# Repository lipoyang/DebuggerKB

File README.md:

DebuggerKB
=========

## 概要
IDEでのデバッグ関連のショートカットキーを並べた専用キーボードです。

* 有線接続(USB HID)と無線接続(BLE HID)の両方に対応。
* LiPoバッテリー(400mAh)と充電回路を内蔵。
* キーマップは最大8レイヤーまで登録でき、切替キーでレイヤーを切り替え可能。
* キーマップはUSB接続時にWebアプリから設定可能。<br>(PC版の Chrome や Edge など Web Serial API に対応したブラウザが必要)
* Nordic nRF52840 搭載。 (Seeed Studio XIAO nRF52840)
* Arduinoベースの独自ファームウェア。 (QMKではありません。)

## キーマップの設定
[Webアプリ](app/DebuggerKB_Config/)から、各レイヤーの名称、LED表示色、キーマップを設定できます。

キーボードをUSB接続すると、HIDと仮想COMポートの複合デバイスになるので、Webアプリから仮想COMポートを選択して接続します。

## デフォルトのキーマップ
初期状態では4つのレイヤーが登録されています。

| キー | 機能名 (例) |Visual Studio | Eclipse | Android Studio | MPLAB X |
| ---- | ---- | ---- | ---- | ---- |---- |
|     | Debug        | F5            | F11      | Shift+F9  | 割当なし |
|       | Run          | Ctrl+F5       | Ctrl+F11 | Shift+F10 | 割当なし |
|  | Continue     | F5            | F8       | F9        | F5      |
|     | Pause        | Ctrl+Alt+Pause| 割当なし  | 割当なし  | Ctrl+Alt+8 |
|      | Stop         | Shift+F5      | Ctrl+F2  | Ctrl+F2   | Shift+F5 |
|  | Step Over    | F10           | F6       | F8        | F8      |
|    | Step Into    | F11           | F5       | F7        | F7      |
|   | Steo Out     | Shift+F11     | F7       | Shift+F8  | Ctrl+F7 |
|     | Run To Cursol| Ctrl+F10      | Ctrl+R   | Alt+F9    | F4      |
|   | Restart      | Ctrl+Shift+F5 | 割当なし  | 割当なし  | 割当なし |

※ 機能名はIDEによって異同があります。詳しくは[こちら](FunctionName.xlsx)。  
※ Pauseキー = Breakキー 

 と  を同時に押しながらUSBケーブルを接続するとキーマップがデフォルト設定に初期化されます。

## キースイッチとキーキャップについて
* キースイッチは Cherry MX スイッチ互換の Keilh BOX スイッチを使用しました。
* デバッガの操作という用途を考慮し、軸種はクリック感のある茶軸を選びました。
* [Kailh Switch Socket](https://shop.yushakobo.jp/products/a01ps) を使用しており、キースイッチの着脱が可能です。
* パターン設計の都合で、キースイッチの向きは North Facing (LED穴が上側) にしました。
* キーキャップは、DSAプロファイルのものを使用しました。
* キーキャップの印字は、[遊舎工房](https://yushakobo.jp/)さんのキーキャップUVプリントサービスを利用しました。
* キーキャップの印字データは、白キーキャップを前提として作成しました。(下地の白インクのデータ無し)

## 筐体について
* ボトムプレートとトッププレートは厚さ2mmのアクリル板(キャスト材)を使用しました。
* アクリル板の加工は、[工房Emerge+](https://www.emergeplus.jp/)さんのレーザー加工サービスを利用しました。
* 四隅の穴はM2ネジ用です。

## プリント基板について
* 基板製造は[PCBGOGO](https://www.pcbgogo.jp/)さんのサービスを利用しました。
* 厚さ1.6mmの両面基板で製造しました。
* 実装は手ハンダです。Seeed XIAO nRF52840 の裏面パッドはスルーホールからハンダ付けしました。

## ファームウェアについて

* ファームウェアは Arduinoベースで作成しました。
* Arduino IDEの「ファイル」＞「環境設定」＞「追加のボードマネージャのURL」に下記URLを追加します。
```
https://files.seeedstudio.com/arduino/package_seeeduino_boards_index.json
```
* 「ツール」＞「ボード」＞「ボードマネージャ」で「Seeed nRF52 Boards」をインストールします。
* 「ツール」＞「ボード」で Seeed nRF52 Boards > Seeed XIAO nRF52840 を選択します。
* Seeed nRF52 mbed-enabled Boards ではないことに注意してください。
* シリアルポートが認識しないときは、USBコネクタの横の小さなリセットボタン(RSTのシルクあり)をダブルクリックしてください。

## 依存ライブラリ
<table>
<tr><td>Adafruit NeoPixel </td><td>要インストール</td></tr>
<tr><td>Adafruit TinyUSB  </td><td>Seeed nRF52 Boards に付属</td></tr>
<tr><td>Adafruit_LittleFS </td><td>Seeed nRF52 Boards に付属</td></tr>
<tr><td>InternalFileSystem</td><td>Seeed nRF52 Boards に付属</td></tr>
<tr><td>Bluefruit         </td><td>Seeed nRF52 Boards に付属</td></tr>
</table>

## ファイル一覧

* hard/
    * DebuggerKB.sch/brd : 回路/基板設計データ(Eagle形式)
    * DebuggerKB.pdf : 回路図(PDF)
    * DebuggerKB.zip : ガーバーデータの圧縮ファイル
    * DebuggerKB_BOM.xlsx : BOMリスト(Excel形式)
* mecha/
    * A5_DebuggerKB.svg : プレート(アクリル板)の加工データ
    * DSA_1u_4x4_DebuggerKB.svg : キーキャップのUV印刷データ
* firm/DebuggerKB/
    * DebuggerKB.ino : キーボードのファームウェア (Arduinoスケッチ)
    * \*.h, \*.cpp: ファームウェアで使用する各種クラス宣言と実装
* app/DebuggerKB_Config/ 
    * index.html : キーマップ設定アプリ (webアプリ)
    * \*.js, \*.png, css/\*, lib/\* : キーマップ設定アプリで使用する各種ファイル

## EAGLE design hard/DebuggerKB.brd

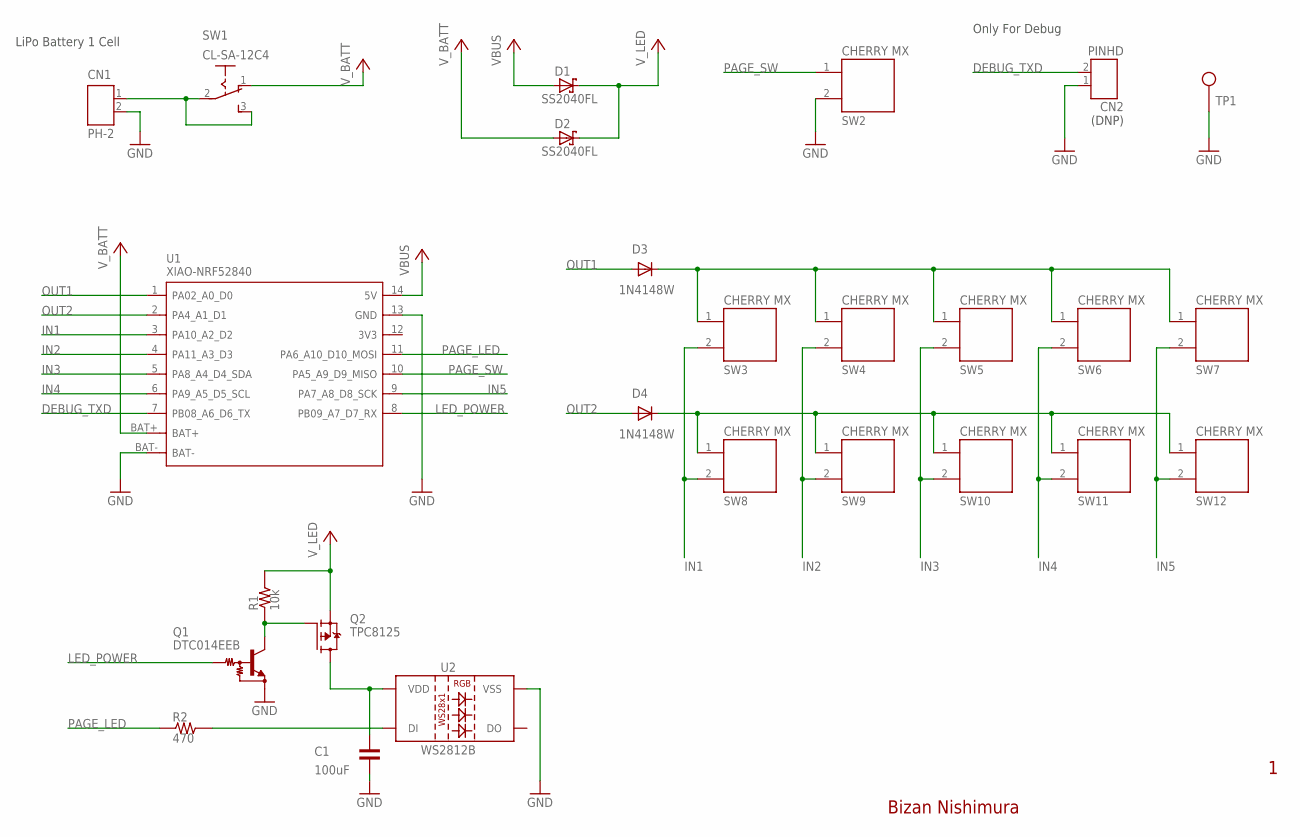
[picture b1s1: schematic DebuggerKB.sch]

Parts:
C1: 100uF; CP3216
CN1: PH-2
CN2: PINHD; 1X02
D1, D2: SS2040FL; SOD123
D3, D4: 1N4148W; SOD123
Q1: DTC014EEB; SOT490
Q2: TPC8125; SO-8
R1: 10k; CP1608
R2: 470; CP1608
SW1: CL-SA-12C4
SW2, SW3, SW4, SW5, SW6, SW7, SW8, SW9, SW10, SW11, SW12: KAILH_SWITCH_SOCKET; SWITCH_SOCKET
TP1: TEST_PIN
U1: XIAO-NRF52840; XIAO-NRF52840-BAT
U2: WS2812B

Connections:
DEBUG_TXD: CN2.2, U1.7 (PB08_A6_D6_TX)
GND: C1.SMD2 (PIN2), CN1.2, CN2.1, Q1.2 (E), SW2.2 (PIN-2), TP1.1, U1.13 (GND), U1.BAT-, U2.3 (VSS)
IN1: SW3.2 (PIN-2), SW8.2 (PIN-2), U1.3 (PA10_A2_D2)
IN2: SW4.2 (PIN-2), SW9.2 (PIN-2), U1.4 (PA11_A3_D3)
IN3: SW5.2 (PIN-2), SW10.2 (PIN-2), U1.5 (PA8_A4_D4_SDA)
IN4: SW6.2 (PIN-2), SW11.2 (PIN-2), U1.6 (PA9_A5_D5_SCL)
IN5: SW7.2 (PIN-2), SW12.2 (PIN-2), U1.9 (PA7_A8_D8_SCK)
LED_POWER: Q1.1 (B), U1.8 (PB09_A7_D7_RX)
unnamed: C1.SMD1 (PIN1), Q2.5 (D), Q2.6 (D), Q2.7 (D), Q2.8 (D), U2.1 (VDD)
unnamed: CN1.1, SW1.2, SW1.3 (S)
unnamed: Q1.3 (C), Q2.4 (G), R1.SMD1 (PIN1)
unnamed: R2.SMD2 (PIN2), U2.4 (DI)
unnamed: D3.C, SW3.1 (PIN-1), SW4.1 (PIN-1), SW5.1 (PIN-1), SW6.1 (PIN-1), SW7.1 (PIN-1)
unnamed: D4.C, SW8.1 (PIN-1), SW9.1 (PIN-1), SW10.1 (PIN-1), SW11.1 (PIN-1), SW12.1 (PIN-1)
OUT1: D3.A, U1.1 (PA02_A0_D0)
OUT2: D4.A, U1.2 (PA4_A1_D1)
PAGE_LED: R2.SMD1 (PIN1), U1.11 (PA6_A10_D10_MOSI)
PAGE_SW: SW2.1 (PIN-1), U1.10 (PA5_A9_D9_MISO)
VBUS: D1.A, U1.14 (5V)
V_BATT: D2.A, SW1.1 (O), U1.BAT+
V_LED: D1.C, D2.C, Q2.1 (S), Q2.2 (S), Q2.3 (S), R1.SMD2 (PIN2)

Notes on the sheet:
Bizan Nishimura
LiPo Battery 1 Cell
(DNP)
Only For Debug

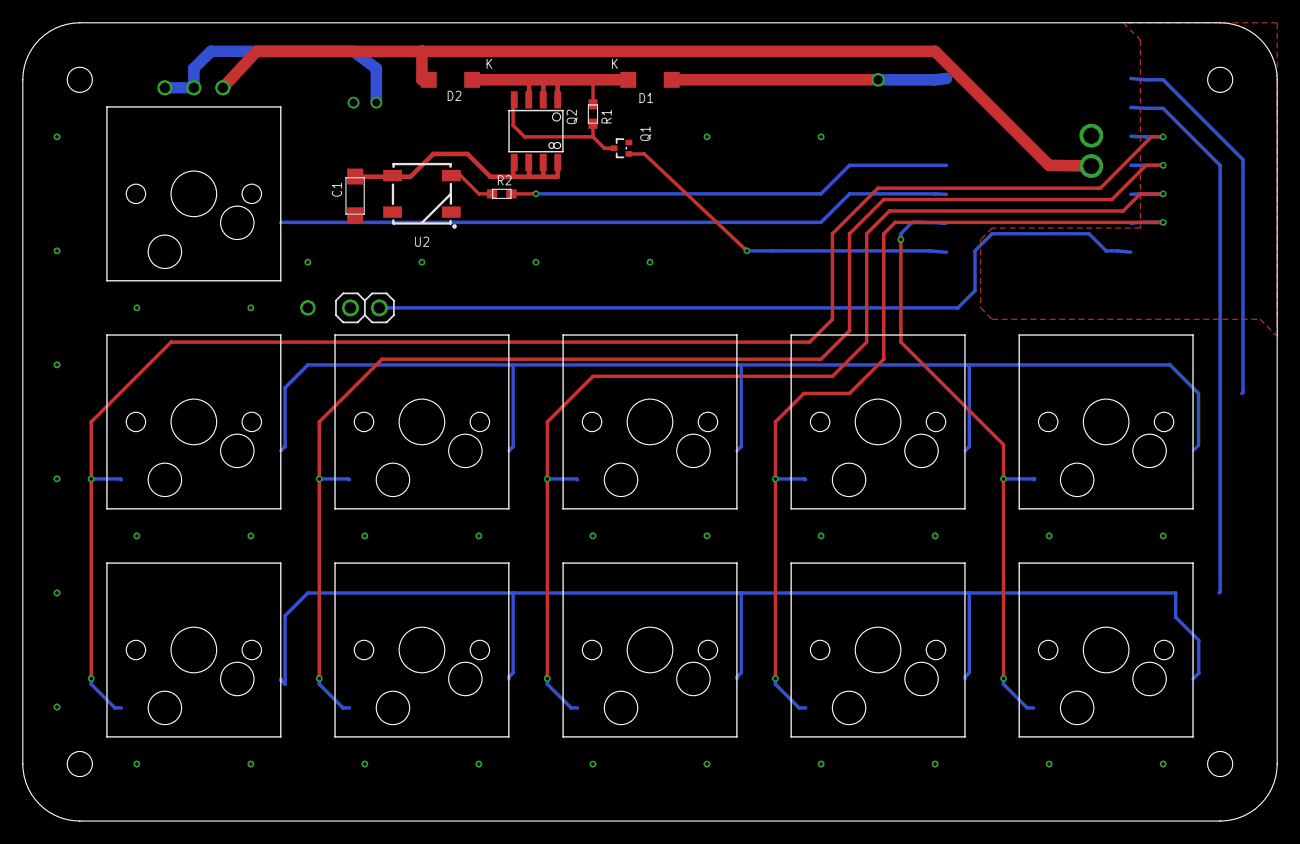
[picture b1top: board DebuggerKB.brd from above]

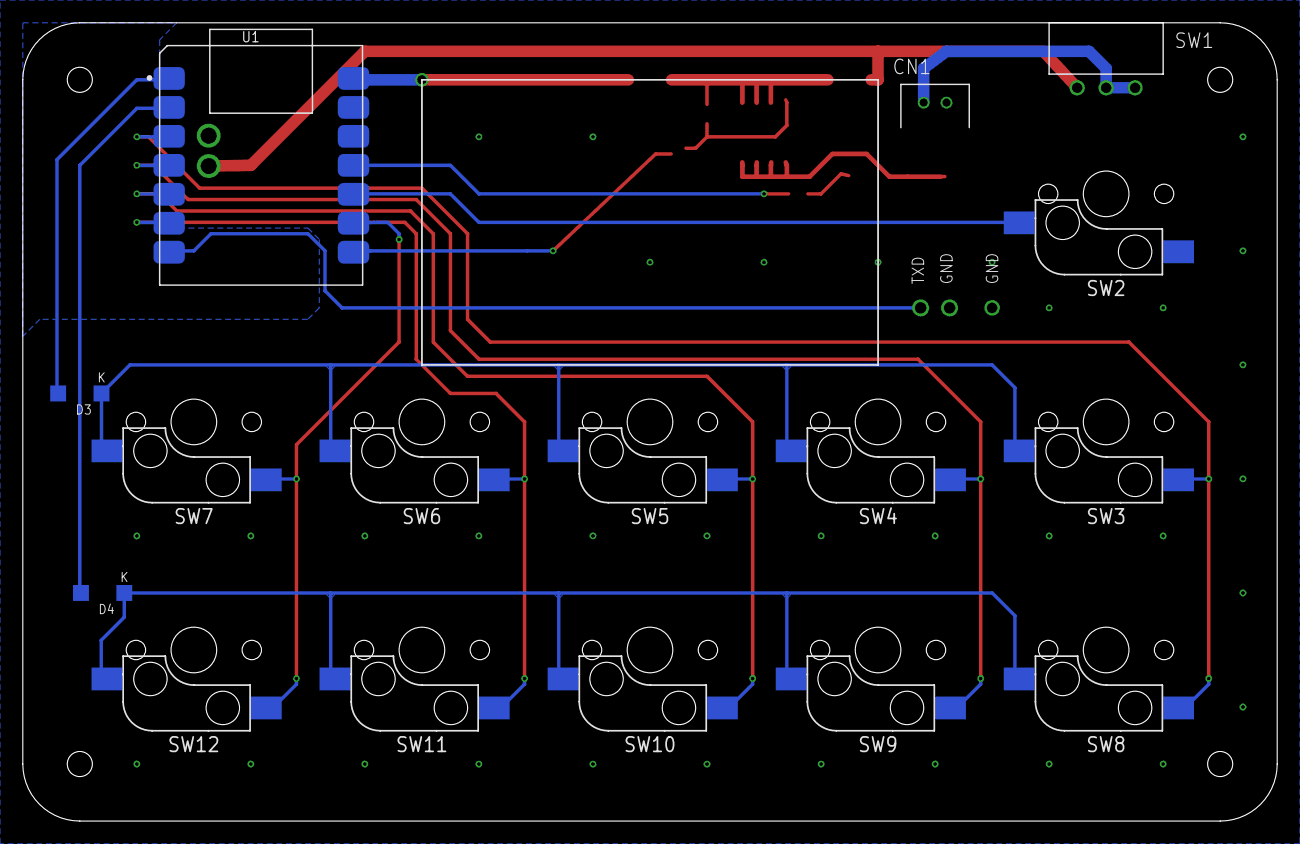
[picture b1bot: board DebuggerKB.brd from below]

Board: 2 copper layers, 110.0 x 70.0 mm, 26 parts (6 on the bottom side), 21 nets.

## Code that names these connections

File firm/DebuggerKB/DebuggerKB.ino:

#include <Adafruit_TinyUSB.h>
#include <Adafruit_NeoPixel.h>
#include "UsbKeyboard.h"
#include "BleKeyboard.h"
#include "SerialCommand.h"
#include "KeyMatrix.h"
#include "Power.h"
#include "Switch.h"
#include "ColorLed.h"
#include "PollingTimer.h"

#define PIN_PAGE_SW      9  // Page Swith pin
#define PIN_LED_POWER    7  // LED Power ON pin
#define PIN_PAGE_LED    10  // LED pin

#define KEY_INTERVAL     5  // Key Interval [msec]

// Page Switch
Switch pageSwitch;
// Page LED
ColorLed pageLed(PIN_PAGE_LED);
// Power Controller
Power power;

// USB Keyboard
UsbKeyboard usbKeyboard;
// BLE Keyboard
BleKeyboard bleKeyboard;
// USB or BLE Keyboard
Keyboard *keyboard;

// Key Matrix
KeyMatrix keyMatrix;
// Serial Command
SerialCommand serialCommand;
// Keymap Storage
KeyMapStorage keyMapStorage;

// Output Pins (for Key Matrix)
int outPin[ROW_NUM] = { 0, 1 };
// Input Pins  (for Key Matrix)
int inPin [COL_NUM] = { 2, 3, 4, 5, 8 };
// Keycode 
uint8_t keyTable[KEY_MAX][KEY_COMBI_MAX];

// is USB connected?
bool isUsbConnected;

// Interval Timer
IntervalTimer interval;

// Initialize
void setup()
{
    // Power
    power.begin(PIN_LED_POWER, PIN_PAGE_SW);
    
    // Page Switch
    pageSwitch.begin(PIN_PAGE_SW);
    
    // Page LED
    if (power.detectVbus()) {
        pageLed.begin(LED_BUS_POWERED);
    } else {
        pageLed.begin(LED_BAT_POWERED);
    }
    
    // begin Key Matrix
    keyMatrix.begin(outPin, inPin);
    
    // detect VBUS
    if (power.detectVbus()) {
        // USB Keyboard
        digitalWrite(LED_GREEN, LOW);
        keyboard = &usbKeyboard;
        isUsbConnected = true;
        
        // Factory Reset?
        if(keyMatrix.pressFactoryReset()){
            pageLed.setColor(COLOR_RED);
            delay(1000);
            keyMapStorage.factoryReset();
            pageLed.setColor(COLOR_GREEN);
            delay(3000);
            NVIC_SystemReset();
        }
        
    } else {
        // BLE Keyboard
        digitalWrite(LED_BLUE,  LOW);
        keyboard = &bleKeyboard;
        isUsbConnected = false;
    }

    // begin HID (USB of BLE)
    keyboard->begin();
    
    // begin Serial Command
    serialCommand.keyMaps = keyMapStorage.keyMaps;
    if(isUsbConnected) serialCommand.begin();
    
    // Keymap Strage
    keyMapStorage.begin();
    keyMapStorage.getKeyTable(keyTable);
    
    // set Keymap to Key Matrix
    keyMatrix.setKeyTable(keyTable);
    
    // show Page LED
    pageLed.setColor(keyMapStorage.getLedColor());
    
    // begin Interval Timer
    interval.set(KEY_INTERVAL);
}

// Main Loop
void loop()
{
    // key interval
    if(!interval.elapsed()) return;

    // page LED control
    pageLed.task();
    
    // check low battery voltage
    bool lowBattery = power.checkLowBattery();
    // check no operation
    bool noOperation = power.checkNoOperation();
    // sleep?
    if(lowBattery || noOperation){
        pageLed.turnOff();
        power.sleep();
    }
    
    // serial command task
    if(isUsbConnected){
        int ret = serialCommand.task();
        if(ret == RET_WRITE){
            keyMapStorage.save();
            keyMapStorage.changePage(false);
            keyMapStorage.getKeyTable(keyTable);
            keyMatrix.setKeyTable(keyTable);
            
            pageLed.setColor(keyMapStorage.getLedColor());
        }
    }
    
    // get page switch event
    int event = pageSwitch.get();
    if(event == SW_EVENT_SHORT){
        keyMapStorage.changePage(true);
        keyMapStorage.getKeyTable(keyTable);
        keyMatrix.setKeyTable(keyTable);
        
        pageLed.setColor(keyMapStorage.getLedColor());
        power.kick();
    }
    else if(event == SW_EVENT_LONG){
        pageLed.turnOnWhile();
        power.kick();
    }

    // skip if hid is not ready
    if ( !keyboard->ready() ) return;

    // scan key matrix
    if(keyMatrix.scan()){
        // press any key?
        if(keyMatrix.pressAnyKey()){
            // wake up
            keyboard->wakeup();
            // get key code
            uint8_t keycode[KEY_CODE_MAX] = { 0 };
            keyMatrix.getKey(keycode);
            
            // keyboard report
            if(keycode[0] != 0){
                keyboard->keyboardReport(keycode);
                
                pageLed.turnOnMoment();
                power.kick();
            }
        }else{
            // key release
            keyboard->keyboardRelease();
        }
    }
}

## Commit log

2023-01-13 add files
2023-01-13 add README
2023-01-13 add to README
2023-01-13 add Switch class
2023-01-13 add NeoPixwl
2023-01-14 add Power class
2023-01-14 add to Power class
2023-01-14 add to Power
2023-01-16 bug fix
2023-01-16 clean up
2023-01-21 add toast message
2023-01-22 modify LED control
2023-01-22 modify LED and Switch control
2023-01-27 add board design
2023-01-28 modify board design
2023-01-30 add plate design
2023-02-04 add BOM
2023-02-11 modify app
2023-02-11 modify firm
2023-02-14 fix README

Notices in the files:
parts and their libraries:
lipoyang_frame: Released under the Creative Commons
Attribution Share-Alike 3.0 License
http://creativecommons.org/licenses/by-sa/3.0
